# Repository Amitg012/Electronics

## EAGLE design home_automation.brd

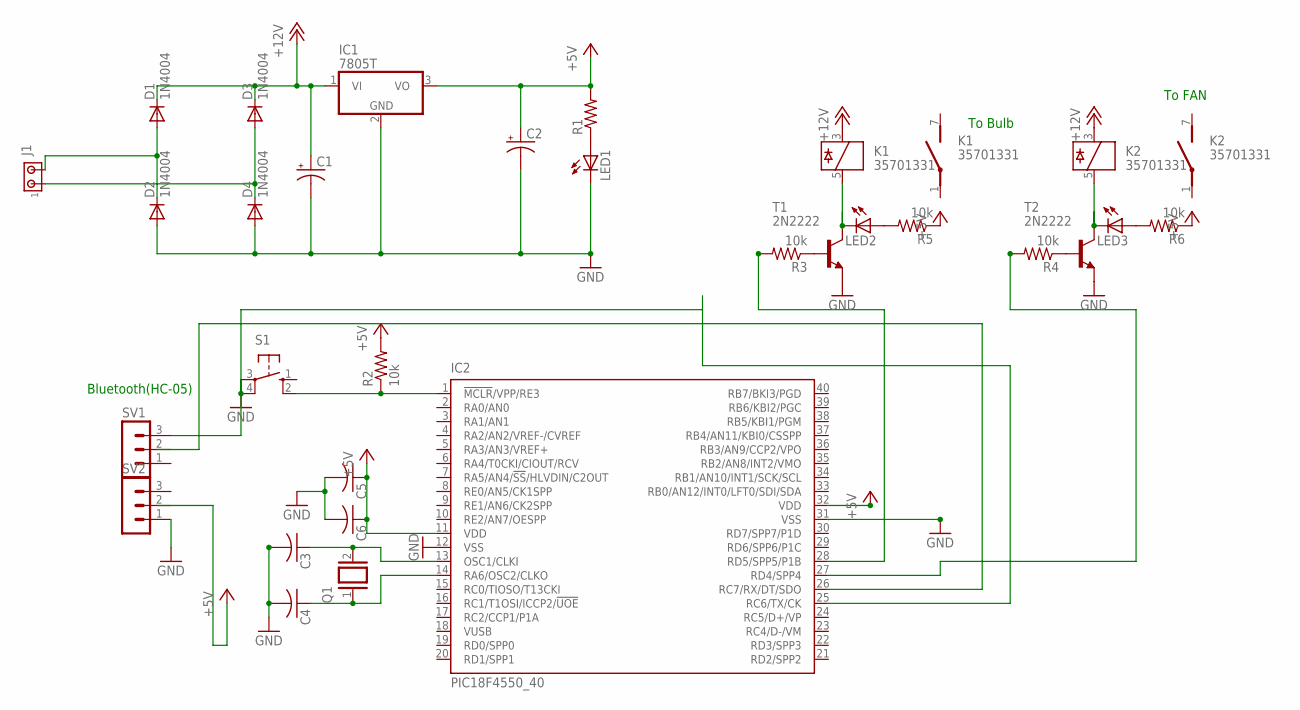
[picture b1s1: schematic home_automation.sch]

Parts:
C1, C2: CPOL-USE3.5-8; E3,5-8
C3, C4, C5, C6: C-US025-024X044; C025-024X044
D1, D2, D3, D4: 1N4004; DO41-10
IC1: 7805T; TO220H
IC2: PIC18F4550_40; DIL40
J1: MTA02-100; 10X02MTA
K1, K2: 35701331; REED
LED1, LED2, LED3: LED5MM
Q1: XTAL/S; QS
R1: R-US_0207/10; 0207/10
R2, R3, R4, R5, R6: 10k; 0207/10
S1: 10-XX; B3F-10XX
SV1, SV2: MA03-1
T1, T2: 2N2222; TO92-EBC-OVAL

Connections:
+5V: C2.+, C5.1, C6.1, IC1.3 (VO), IC2.11 (VDD), IC2.32 (VDD), R1.2, R2.2, R5.1, R6.1
+12V: C1.+, D1.C, D3.C, IC1.1 (VI), K1.3, K2.3
GND: C1.-, C2.-, C3.2, C4.2, C5.2, C6.2, D2.A, D4.A, IC1.2 (GND), IC2.12 (VSS), IC2.31 (VSS), LED1.K (C), S1.3, S1.4 (P1), SV2.1, T1.E, T2.E
unnamed: IC2.25 (RC6/TX/CK), SV1.3
unnamed: D1.A, D2.C, J1.2
unnamed: D3.A, D4.C, J1.1
unnamed: C4.1, IC2.14 (RA6/OSC2/CLKO), Q1.1
unnamed: C3.1, IC2.13 (OSC1/CLKI), Q1.2
unnamed: LED1.A, R1.1
unnamed: LED2.A, R5.2
unnamed: R4.1, T2.B
unnamed: K2.5, LED3.K (C), T2.C
unnamed: R3.1, T1.B
unnamed: IC2.1 (!MCLR!/VPP/RE3), R2.1, S1.2 (S1)
unnamed: LED3.A, R6.2
unnamed: IC2.27 (RD4/SPP4), R4.2
unnamed: K1.5, LED2.K (C), T1.C
unnamed: IC2.28 (RD5/SPP5/P1B), R3.2

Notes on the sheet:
To Bulb
To FAN
Bluetooth(HC-05)

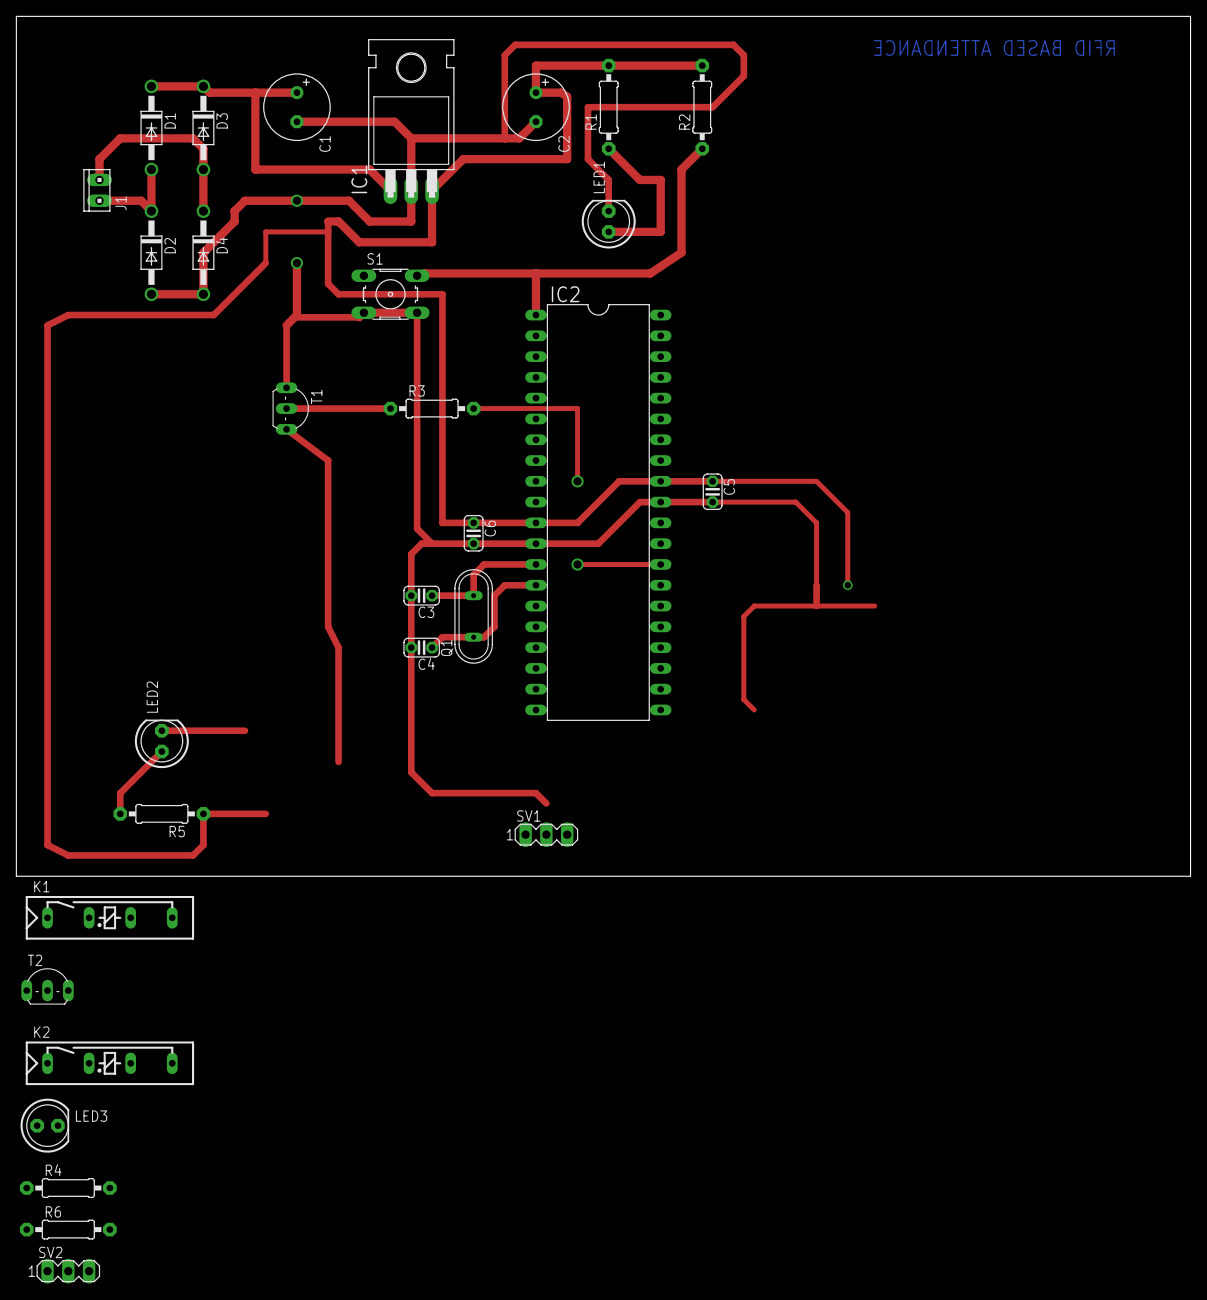
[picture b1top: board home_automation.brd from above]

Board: 2 copper layers, 143.5 x 105.1 mm, 30 parts (0 on the bottom side), 18 nets.

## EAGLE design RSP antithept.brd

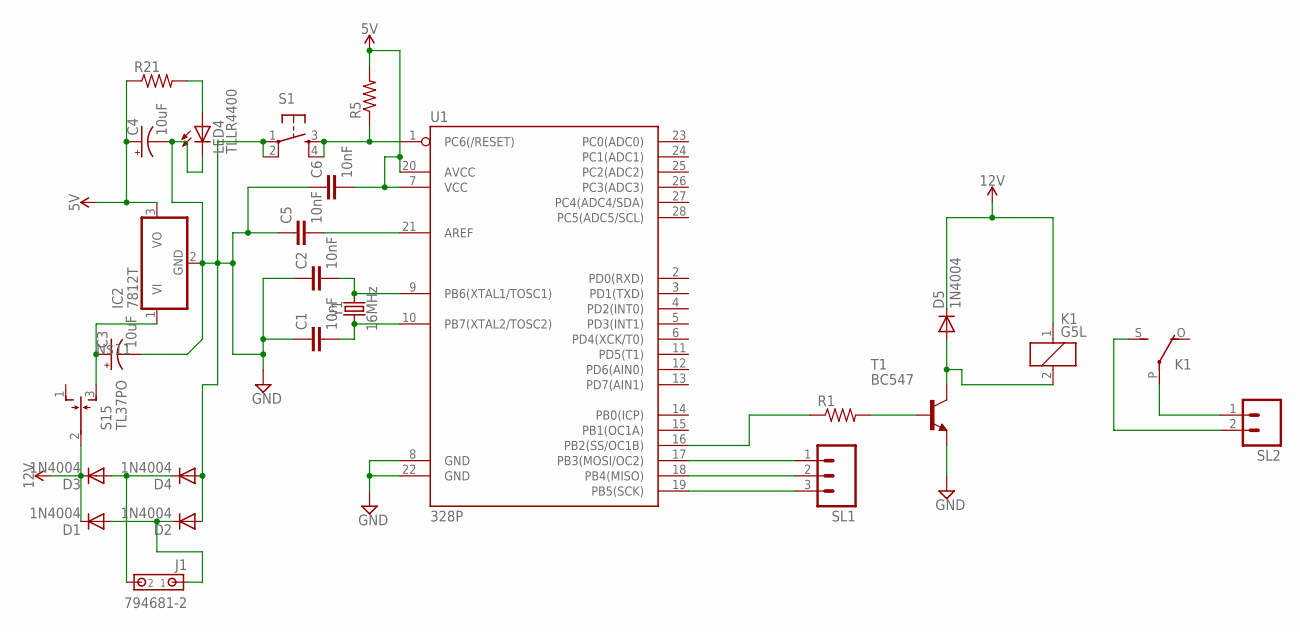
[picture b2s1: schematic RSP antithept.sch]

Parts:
C1, C2, C5, C6: 10nF; CAP-PTH-10MM
C3, C4: 10uF; CPOL-RADIAL-2.5MM-5MM-KIT
D1, D2, D3, D4, D5: 1N4004; DO41-10
IC2: 7812T; TO220H
J1: 794681-2
K1: G5L; G5LE
LED4: TLLR4400; LED3MM
R1: R-US_0207/9; 0207/9
R5, R21: R-US_0207/12; 0207/12
S1: TAC_SWITCHPTH; TACTILE-PTH
S15: TL37PO; TL3XPO
SL1: MA03; 03P
SL2: MA02; 02PA
T1: BC547; TO92
U1: 328P; DIP28
Y1: 16MHz; HC49US

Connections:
5V: C4.1 (+), C6.2, IC2.3 (VO), R5.2, R21.1, U1.7 (VCC), U1.20 (AVCC)
12V: D1.C, D3.C, D5.C, K1.1, S15.2
GND: C1.1, C2.1, C3.2 (-), C4.2 (-), C5.1, C6.1, D2.A, D4.A, IC2.2 (GND), LED4.K (C), S1.1, S1.2, T1.1 (E), U1.8 (GND), U1.22 (GND)
unnamed: SL1.1, U1.17 (PB3(MOSI/OC2))
unnamed: SL1.2, U1.18 (PB4(MISO))
unnamed: C2.2, U1.9 (PB6(XTAL1/TOSC1)), Y1.2
unnamed: C1.2, U1.10 (PB7(XTAL2/TOSC2)), Y1.1
unnamed: LED4.A, R21.2
unnamed: C5.2, U1.21 (AREF)
unnamed: SL1.3, U1.19 (PB5(SCK))
unnamed: R1.1, U1.16 (PB2(SS/OC1B))
unnamed: R5.1, S1.3, S1.4, U1.1 (PC6(/RESET))
unnamed: D3.A, D4.C, J1.2
unnamed: C3.1 (+), IC2.1 (VI), S15.3 (S)
unnamed: R1.2, T1.2 (B)
unnamed: D5.A, K1.2, T1.3 (C)
unnamed: K1.S, SL2.2
unnamed: K1.P, SL2.1
unnamed: D1.A, D2.C, J1.1

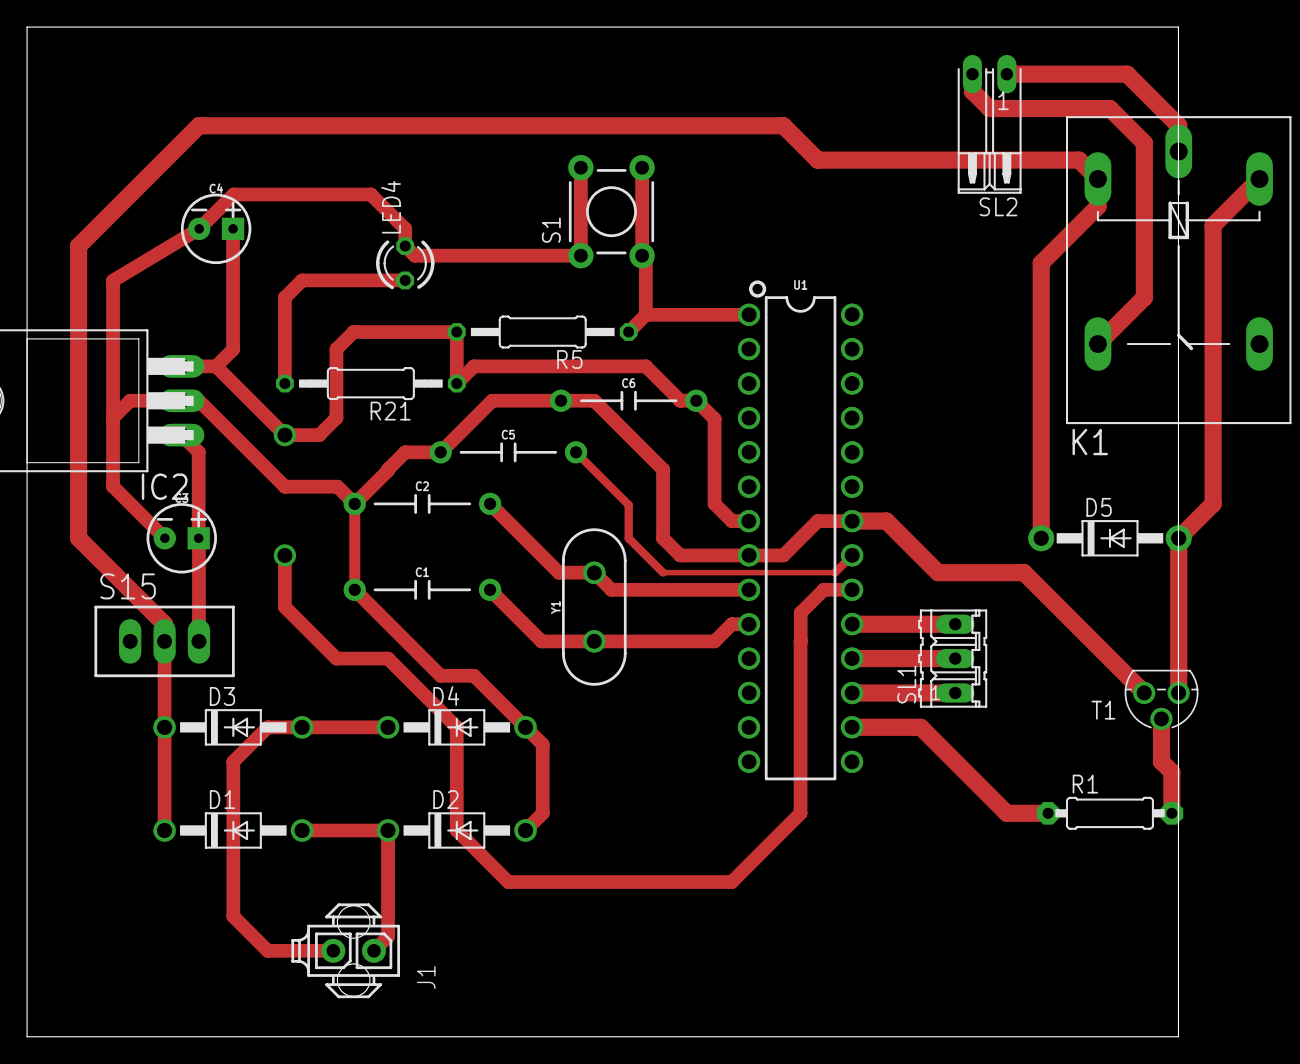
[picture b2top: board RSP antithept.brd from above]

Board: 2 copper layers, 85.1 x 74.6 mm, 25 parts (0 on the bottom side), 19 nets.

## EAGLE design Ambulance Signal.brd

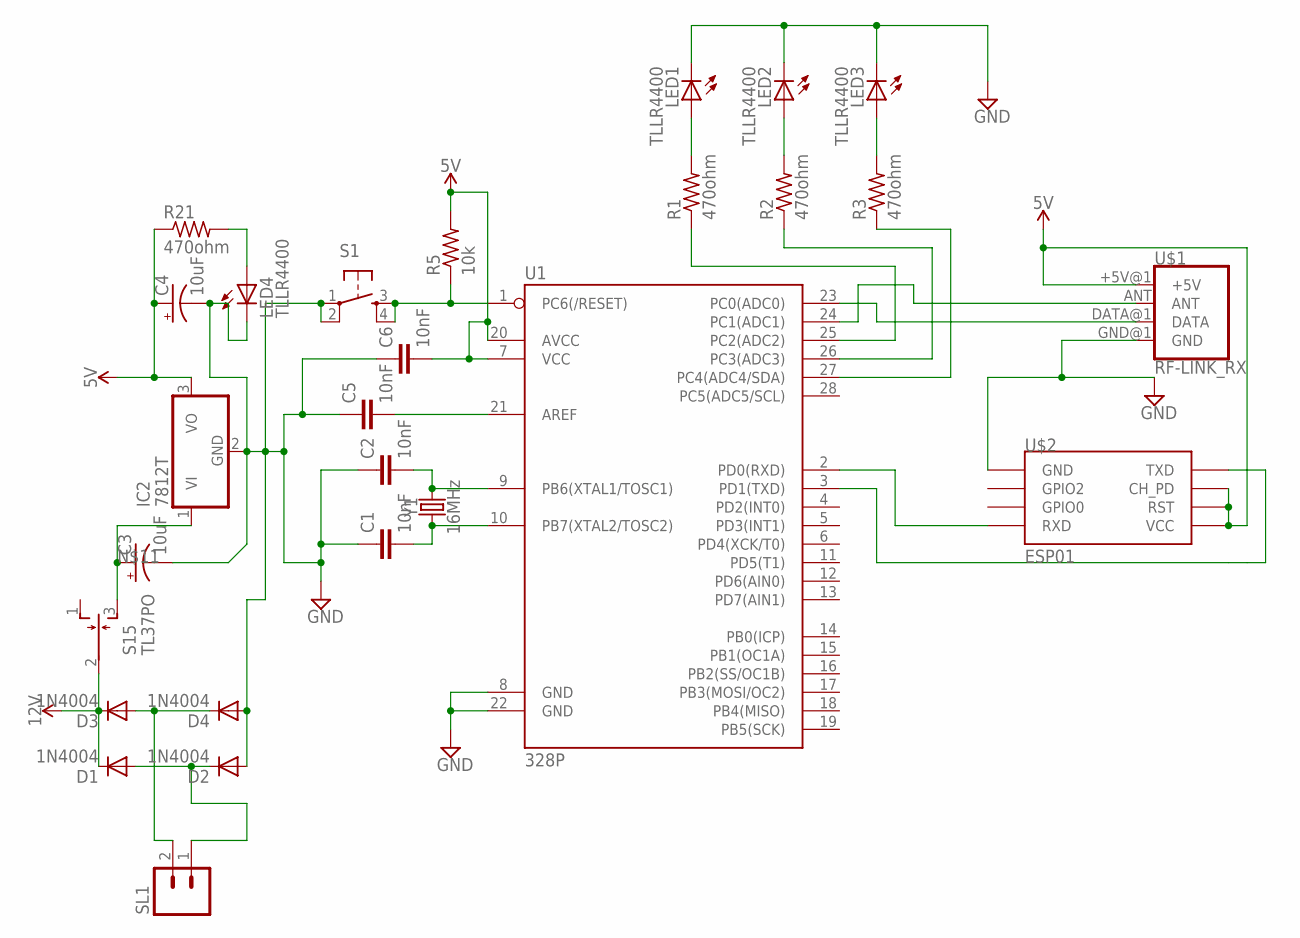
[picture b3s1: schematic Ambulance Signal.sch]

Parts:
C1, C2, C5, C6: 10nF; CAP-PTH-10MM
C3, C4: 10uF; CPOL-RADIAL-2.5MM-5MM-KIT
D1, D2, D3, D4: 1N4004; DO41-10
IC2: 7812T; TO220H
LED1, LED2, LED3, LED4: TLLR4400; LED3MM
R1, R2, R3, R21: 470ohm; 0207/12
R5: 10k; 0207/12
S1: TAC_SWITCHPTH; TACTILE-PTH
S15: TL37PO; TL3XPO
SL1: MA02; 02PA
U1: 328P; DIP28
U$1: RF-LINK_RX
U$2: ESP01
Y1: 16MHz; HC49US

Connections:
5V: C4.1 (+), C6.2, IC2.3 (VO), R5.2, R21.1, U1.7 (VCC), U1.20 (AVCC), U$1.+5V@1 (+5V), U$2.CH_PD, U$2.RST, U$2.VCC
12V: D1.C, D3.C, S15.2
GND: C1.1, C2.1, C3.2 (-), C4.2 (-), C5.1, C6.1, D2.A, D4.A, IC2.2 (GND), LED1.K (C), LED2.K (C), LED3.K (C), LED4.K (C), S1.1, S1.2, U1.8 (GND), U1.22 (GND), U$1.GND@1 (GND), U$2.GND
unnamed: U1.24 (PC1(ADC1)), U$1.ANT
unnamed: U1.23 (PC0(ADC0)), U$1.DATA@1 (DATA)
unnamed: C2.2, U1.9 (PB6(XTAL1/TOSC1)), Y1.2
unnamed: C1.2, U1.10 (PB7(XTAL2/TOSC2)), Y1.1
unnamed: LED4.A, R21.2
unnamed: C5.2, U1.21 (AREF)
unnamed: R5.1, S1.3, S1.4, U1.1 (PC6(/RESET))
unnamed: D3.A, D4.C, SL1.2
unnamed: C3.1 (+), IC2.1 (VI), S15.3 (S)
unnamed: U1.2 (PD0(RXD)), U$2.RX (RXD)
unnamed: U1.3 (PD1(TXD)), U$2.TX (TXD)
unnamed: R1.1, U1.25 (PC2(ADC2))
unnamed: R2.1, U1.26 (PC3(ADC3))
unnamed: R3.1, U1.27 (PC4(ADC4/SDA))
unnamed: LED1.A, R1.2
unnamed: LED2.A, R2.2
unnamed: LED3.A, R3.2
unnamed: D1.A, D2.C, SL1.1

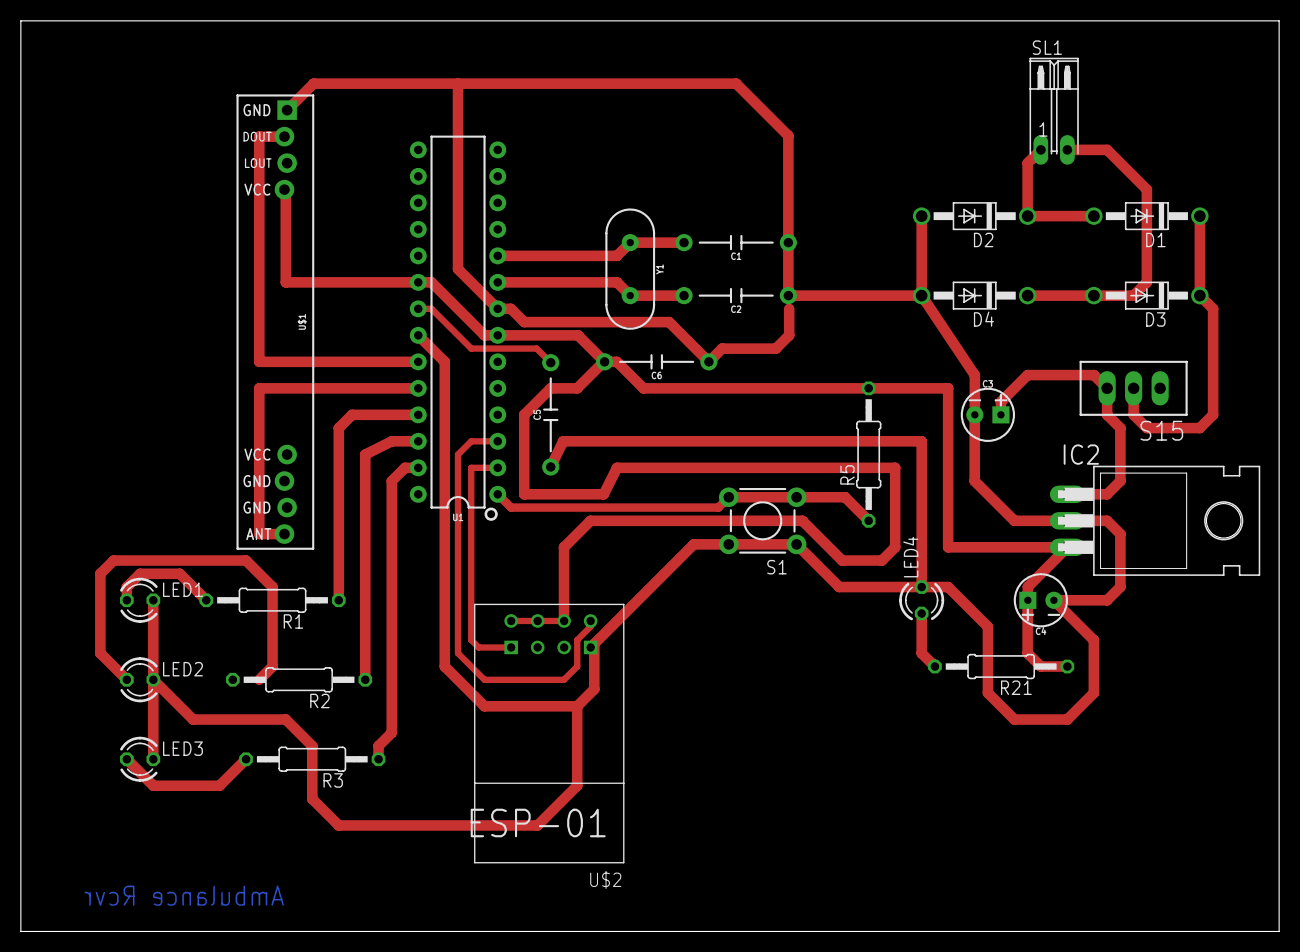
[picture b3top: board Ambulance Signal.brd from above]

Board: 2 copper layers, 120.6 x 87.3 mm, 27 parts (0 on the bottom side), 21 nets.

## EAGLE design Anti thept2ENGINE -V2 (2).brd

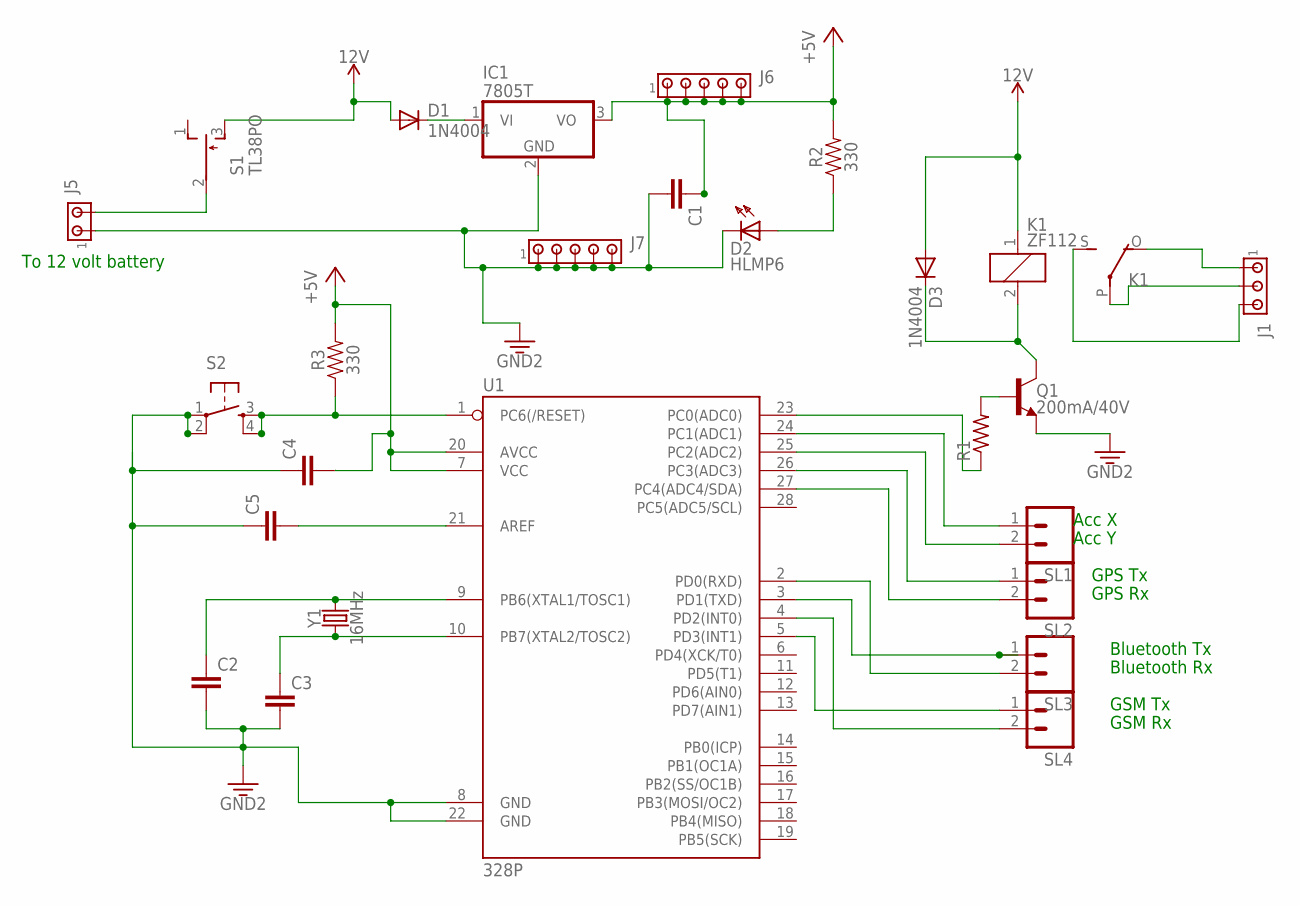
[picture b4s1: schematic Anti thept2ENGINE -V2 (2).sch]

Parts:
C1, C2, C3, C4, C5: C5/2.5; C5B2.5
D1, D3: 1N4004; DO41-10
D2: HLMP6
IC1: 7805T; TO220H
J1: MTA03-156; 1X3MTA
J5: MTA02-156; 1X2MTA
J6, J7: MTA05-100; 10X05MTA
K1: ZF112
Q1: 200mA/40V; TO-92
R1: R-US_0204/7; 0204/7
R2, R3: 330; AXIAL-0.3
S1: TL38PO; TL3XPO
S2: TAC_SWITCHPTH; TACTILE-PTH
SL1, SL2, SL3, SL4: MA02; 02PA
U1: 328P; DIP28
Y1: 16MHz; HC49US

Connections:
3.3V: C1.2, C2.2, C3.2, C4.1, C5.1, D2.K, IC1.2 (GND), J5.1, J7.1, J7.2, J7.3, J7.4, J7.5, Q1.1 (E), S2.1, S2.2, U1.8 (GND), U1.22 (GND)
12V: D1.A, D3.A, K1.1, S1.3 (S)
+5V: C1.1, C4.2, IC1.3 (VO), J6.1, J6.2, J6.3, J6.4, J6.5, R2.P$2 (2), R3.P$2 (2), U1.7 (VCC), U1.20 (AVCC)
unnamed: J1.1, K1.O
unnamed: J1.2, K1.P
unnamed: Q1.2 (B), R1.2
unnamed: D3.C, K1.2, Q1.3 (C)
unnamed: J1.3, K1.S
unnamed: R1.1, U1.23 (PC0(ADC0))
unnamed: D2.A, R2.P$1 (1)
unnamed: C3.1, U1.10 (PB7(XTAL2/TOSC2)), Y1.1
unnamed: SL1.1, U1.24 (PC1(ADC1))
unnamed: R3.P$1 (1), S2.3, S2.4, U1.1 (PC6(/RESET))
unnamed: SL1.2, U1.25 (PC2(ADC2))
unnamed: C5.2, U1.21 (AREF)
unnamed: SL2.1, U1.26 (PC3(ADC3))
unnamed: J5.2, S1.2
unnamed: SL3.2, U1.2 (PD0(RXD))
unnamed: D1.C, IC1.1 (VI)
unnamed: SL3.1, U1.3 (PD1(TXD))
unnamed: C2.1, U1.9 (PB6(XTAL1/TOSC1)), Y1.2
unnamed: SL2.2, U1.27 (PC4(ADC4/SDA))
unnamed: SL4.2, U1.4 (PD2(INT0))
unnamed: SL4.1, U1.5 (PD3(INT1))

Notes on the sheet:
Bluetooth Tx
Bluetooth Rx
GPS Tx
GPS Rx
Acc X
Acc Y
GSM Tx
GSM Rx
To 12 volt battery

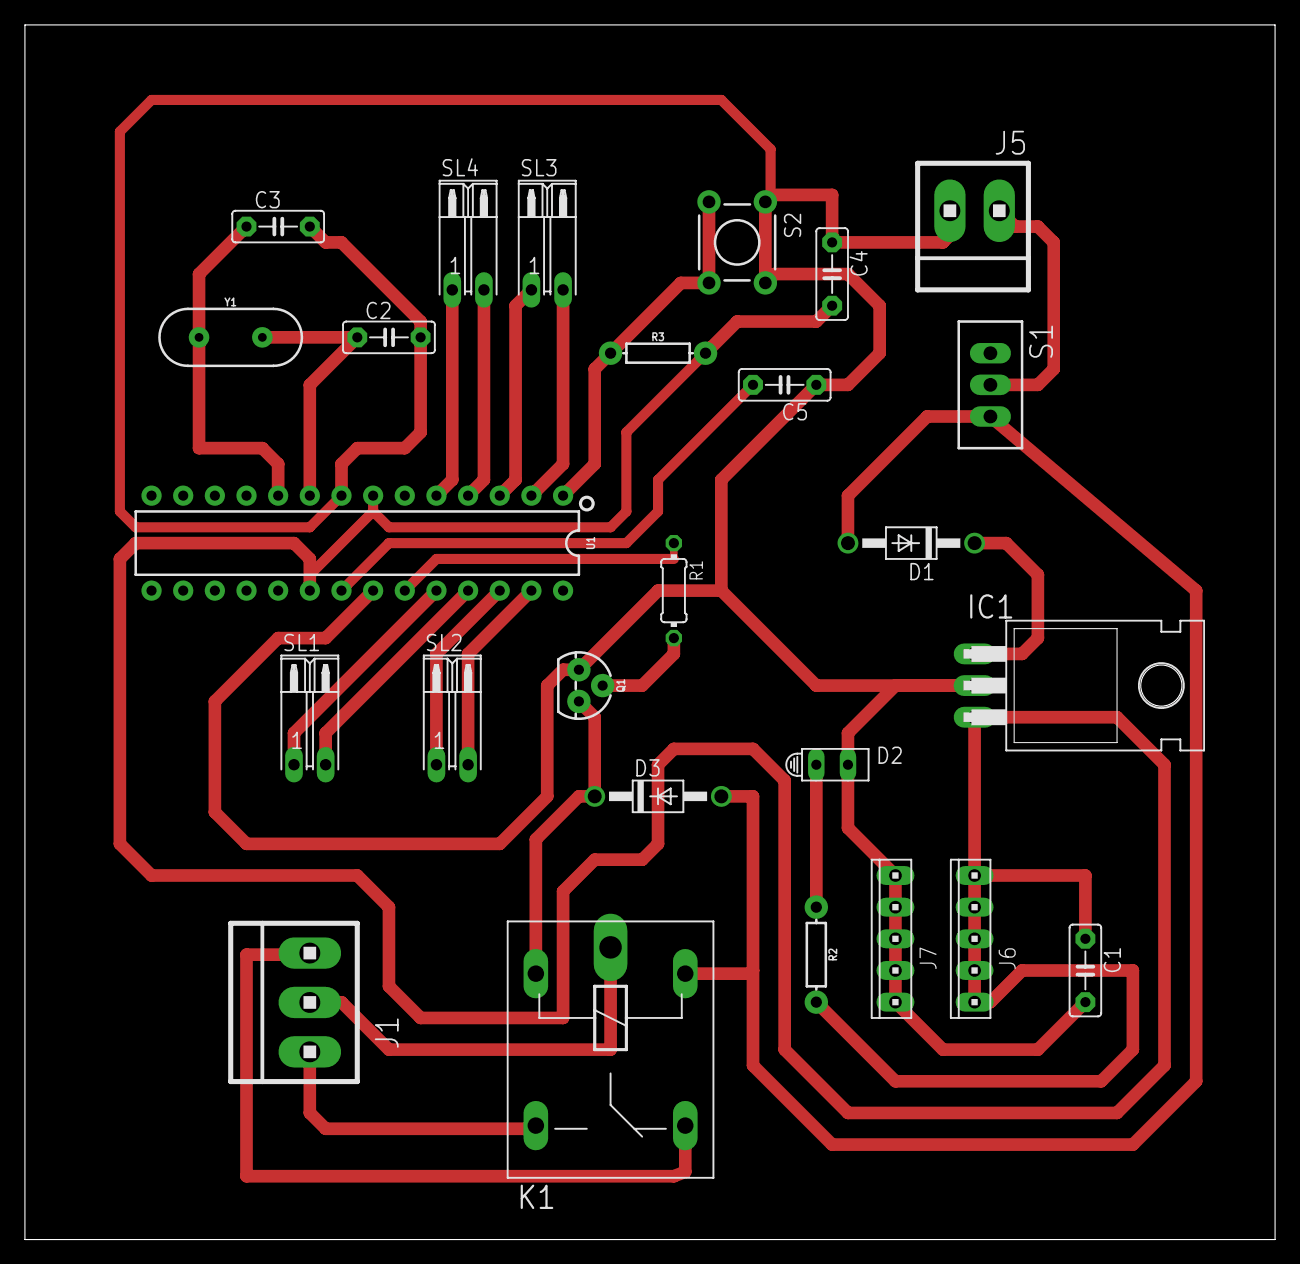
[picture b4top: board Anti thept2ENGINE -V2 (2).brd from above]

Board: 2 copper layers, 100.3 x 97.5 mm, 26 parts (0 on the bottom side), 24 nets.

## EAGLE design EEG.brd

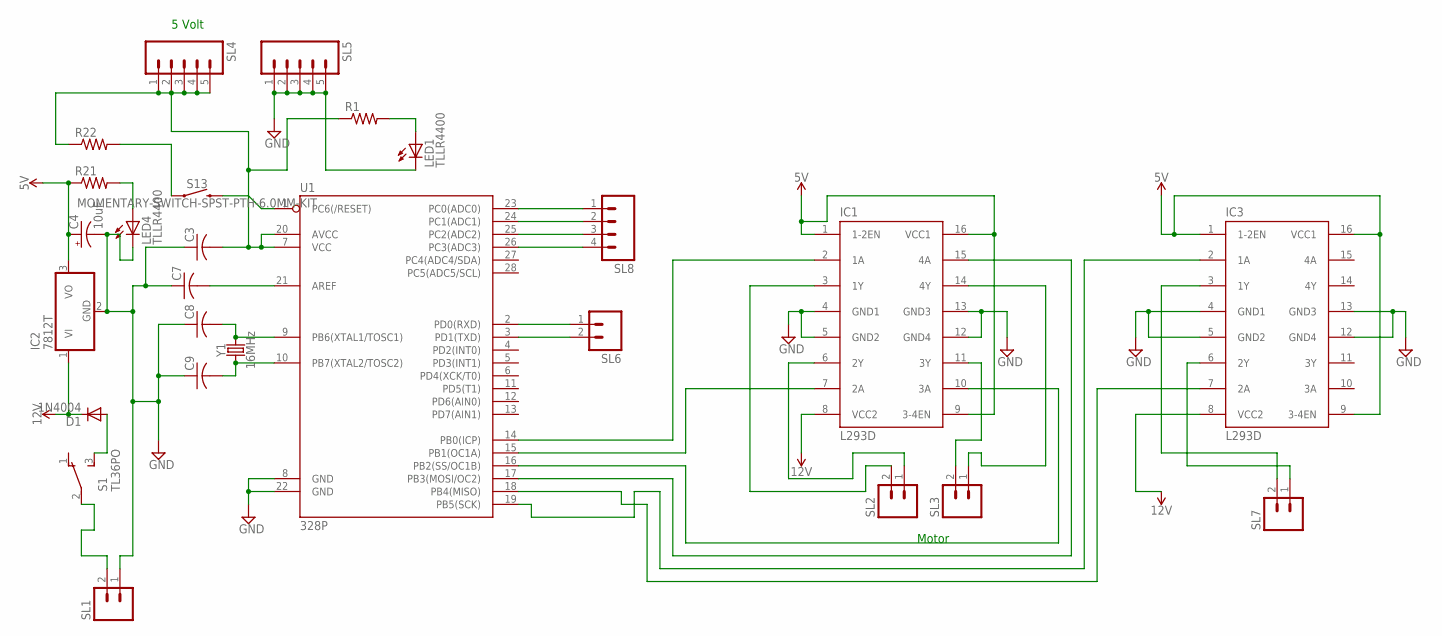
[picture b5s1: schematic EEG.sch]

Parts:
C3, C7, C8, C9: C-US025-025X050; C025-025X050
C4: 10uF; CPOL-RADIAL-2.5MM-5MM-KIT
D1: 1N4004; DO41-10
IC1, IC3: L293D; DIL16
IC2: 7812T; TO220H
LED1, LED4: TLLR4400; LED3MM
R1, R21, R22: R-US_0207/12; 0207/12
S1: TL36PO; TL3XPO
S13: MOMENTARY-SWITCH-SPST-PTH-6.0MM-KIT; TACTILE_SWITCH_PTH_6.0MM_KIT
SL1, SL2, SL3, SL6, SL7: MA02; 02PA
SL4, SL5: MA05; 05PA
SL8: MA04; 04PA
U1: 328P; DIP28
Y1: 16MHz; HC49US

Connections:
5V: C4.1 (+), IC1.1 (1-2EN), IC1.9 (3-4EN), IC1.16 (VCC1), IC2.3 (VO), IC3.1 (1-2EN), IC3.9 (3-4EN), IC3.16 (VCC1), R21.1
12V: D1.C, IC1.8 (VCC2), IC2.1 (VI), IC3.8 (VCC2)
GND: C3.1, C4.2 (-), C7.1, C8.1, C9.1, IC1.4 (GND1), IC1.5 (GND2), IC1.12 (GND4), IC1.13 (GND3), IC2.2 (GND), IC3.4 (GND1), IC3.5 (GND2), IC3.12 (GND4), IC3.13 (GND3), LED1.K (C), LED4.K (C), SL1.1, SL5.1, SL5.2, SL5.3, SL5.4, SL5.5, U1.8 (GND), U1.22 (GND)
unnamed: C7.2, U1.21 (AREF)
unnamed: S1.2, SL1.2
unnamed: C8.2, U1.9 (PB6(XTAL1/TOSC1)), Y1.2
unnamed: C9.2, U1.10 (PB7(XTAL2/TOSC2)), Y1.1
unnamed: LED4.A, R21.2
unnamed: D1.A, S1.3 (S)
unnamed: IC1.3 (1Y), SL2.2
unnamed: R22.2, S13.1
unnamed: S13.3 (2), U1.1 (PC6(/RESET))
unnamed: IC3.2 (1A), U1.19 (PB5(SCK))
unnamed: IC3.7 (2A), U1.18 (PB4(MISO))
unnamed: IC3.3 (1Y), SL7.2
unnamed: IC1.2 (1A), U1.14 (PB0(ICP))
unnamed: IC1.7 (2A), U1.15 (PB1(OC1A))
unnamed: IC1.10 (3A), U1.16 (PB2(SS/OC1B))
unnamed: IC1.15 (4A), U1.17 (PB3(MOSI/OC2))
unnamed: C3.2, R1.1, R22.1, SL4.1, SL4.2, SL4.3, SL4.4, SL4.5, U1.7 (VCC), U1.20 (AVCC)
unnamed: IC3.6 (2Y), SL7.1
unnamed: LED1.A, R1.2
unnamed: SL6.1, U1.2 (PD0(RXD))
unnamed: SL6.2, U1.3 (PD1(TXD))
unnamed: SL8.1, U1.23 (PC0(ADC0))
unnamed: SL8.2, U1.24 (PC1(ADC1))
unnamed: SL8.3, U1.25 (PC2(ADC2))
unnamed: SL8.4, U1.26 (PC3(ADC3))
unnamed: IC1.14 (4Y), SL3.1
unnamed: IC1.6 (2Y), SL2.1
unnamed: IC1.11 (3Y), SL3.2

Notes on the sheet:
Motor
5 Volt

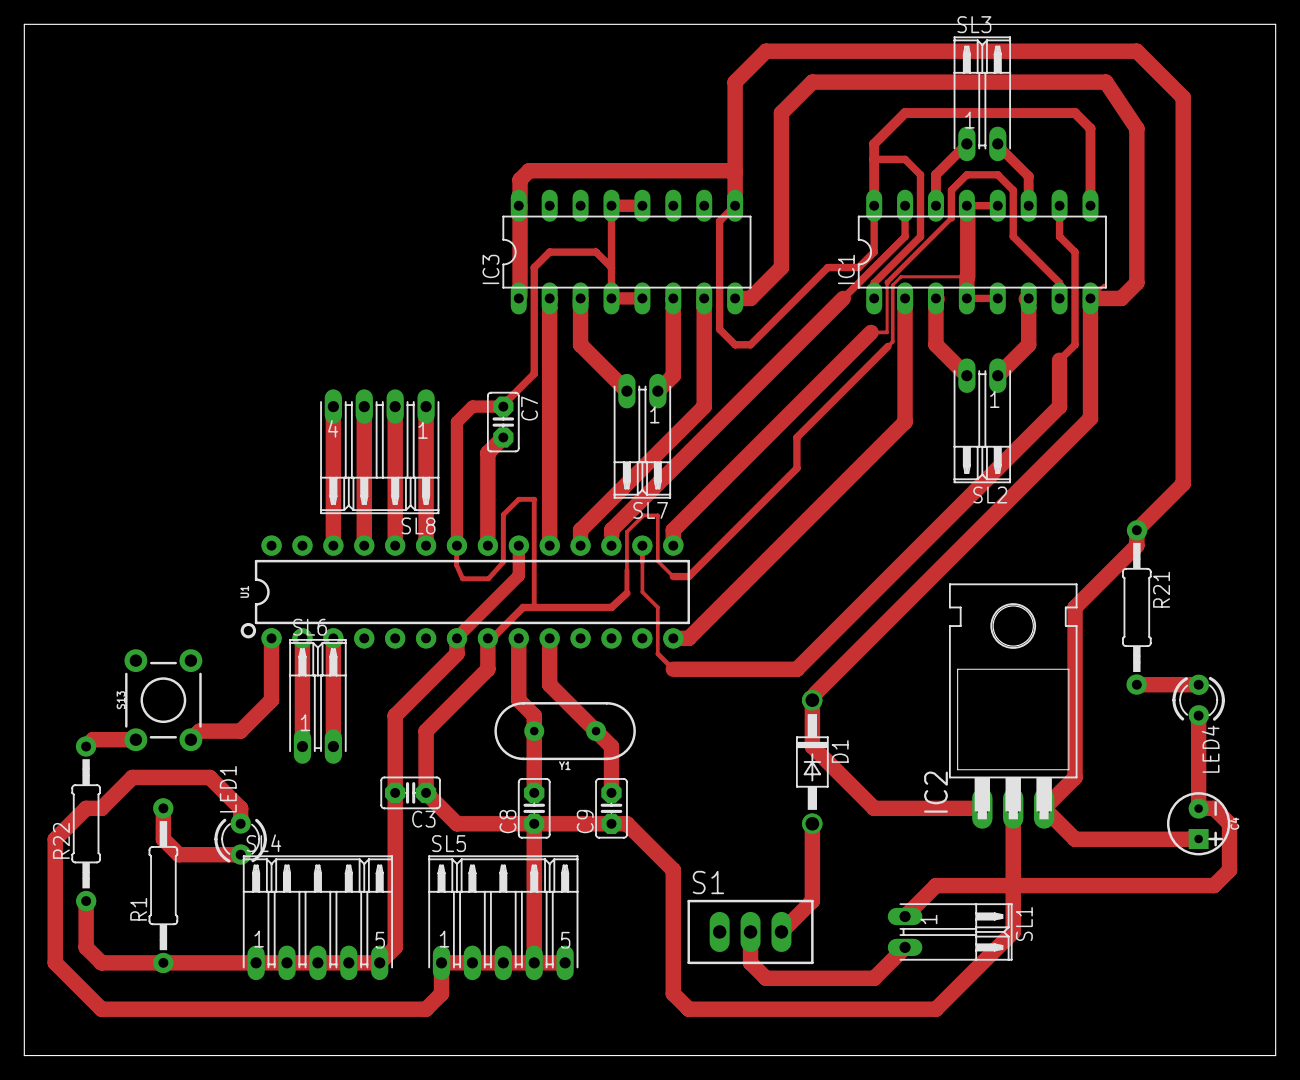
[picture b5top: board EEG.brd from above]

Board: 2 copper layers, 102.8 x 84.8 mm, 26 parts (0 on the bottom side), 31 nets.

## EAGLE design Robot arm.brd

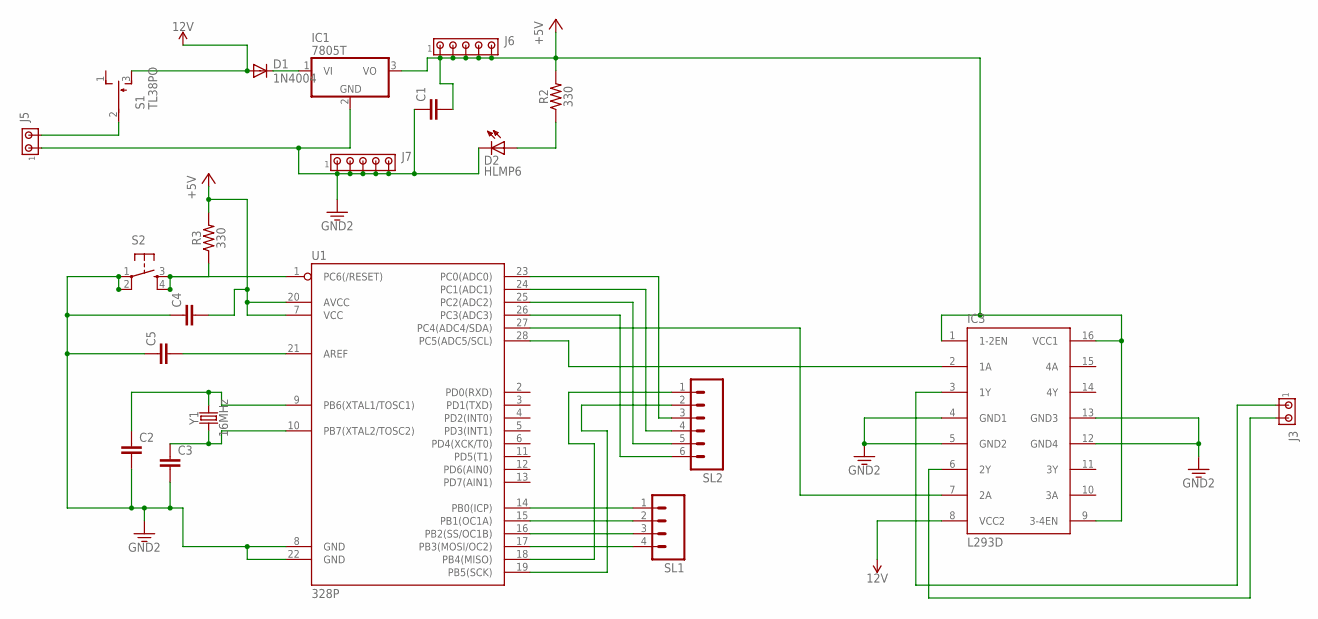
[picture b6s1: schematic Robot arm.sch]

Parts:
C1, C2, C3, C4, C5: C5/2.5; C5B2.5
D1: 1N4004; DO41-10
D2: HLMP6
IC1: 7805T; TO220H
IC3: L293D; DIL16
J3, J5: MTA02-156; 1X2MTA
J6, J7: MTA05-100; 10X05MTA
R2, R3: 330; AXIAL-0.3
S1: TL38PO; TL3XPO
S2: TAC_SWITCHPTH; TACTILE-PTH
SL1: MA04; 04PA
SL2: MA06; 06PA
U1: 328P; DIP28
Y1: 16MHz; HC49US

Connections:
3.3V: C1.1, C2.2, C3.2, C4.1, C5.1, D2.K, IC1.2 (GND), IC3.4 (GND1), IC3.5 (GND2), IC3.12 (GND4), IC3.13 (GND3), J5.1, J7.1, J7.2, J7.3, J7.4, J7.5, S2.1, S2.2, U1.8 (GND), U1.22 (GND)
12V: D1.A, IC3.8 (VCC2), S1.3 (S)
+5V: C1.2, C4.2, IC1.3 (VO), IC3.1 (1-2EN), IC3.9 (3-4EN), IC3.16 (VCC1), J6.1, J6.2, J6.3, J6.4, J6.5, R2.P$2 (2), R3.P$2 (2), U1.7 (VCC), U1.20 (AVCC)
unnamed: IC3.7 (2A), U1.27 (PC4(ADC4/SDA))
unnamed: SL1.1, U1.14 (PB0(ICP))
unnamed: SL1.2, U1.15 (PB1(OC1A))
unnamed: SL1.3, U1.16 (PB2(SS/OC1B))
unnamed: SL1.4, U1.17 (PB3(MOSI/OC2))
unnamed: SL2.3, U1.23 (PC0(ADC0))
unnamed: D2.A, R2.P$1 (1)
unnamed: IC3.2 (1A), U1.28 (PC5(ADC5/SCL))
unnamed: SL2.4, U1.24 (PC1(ADC1))
unnamed: R3.P$1 (1), S2.3, S2.4, U1.1 (PC6(/RESET))
unnamed: C3.1, U1.10 (PB7(XTAL2/TOSC2)), Y1.1
unnamed: C5.2, U1.21 (AREF)
unnamed: IC3.3 (1Y), J3.1
unnamed: J5.2, S1.2
unnamed: IC3.6 (2Y), J3.2
unnamed: D1.C, IC1.1 (VI)
unnamed: SL2.5, U1.25 (PC2(ADC2))
unnamed: SL2.6, U1.26 (PC3(ADC3))
unnamed: SL2.1, U1.18 (PB4(MISO))
unnamed: SL2.2, U1.19 (PB5(SCK))
unnamed: C2.1, U1.9 (PB6(XTAL1/TOSC1)), Y1.2

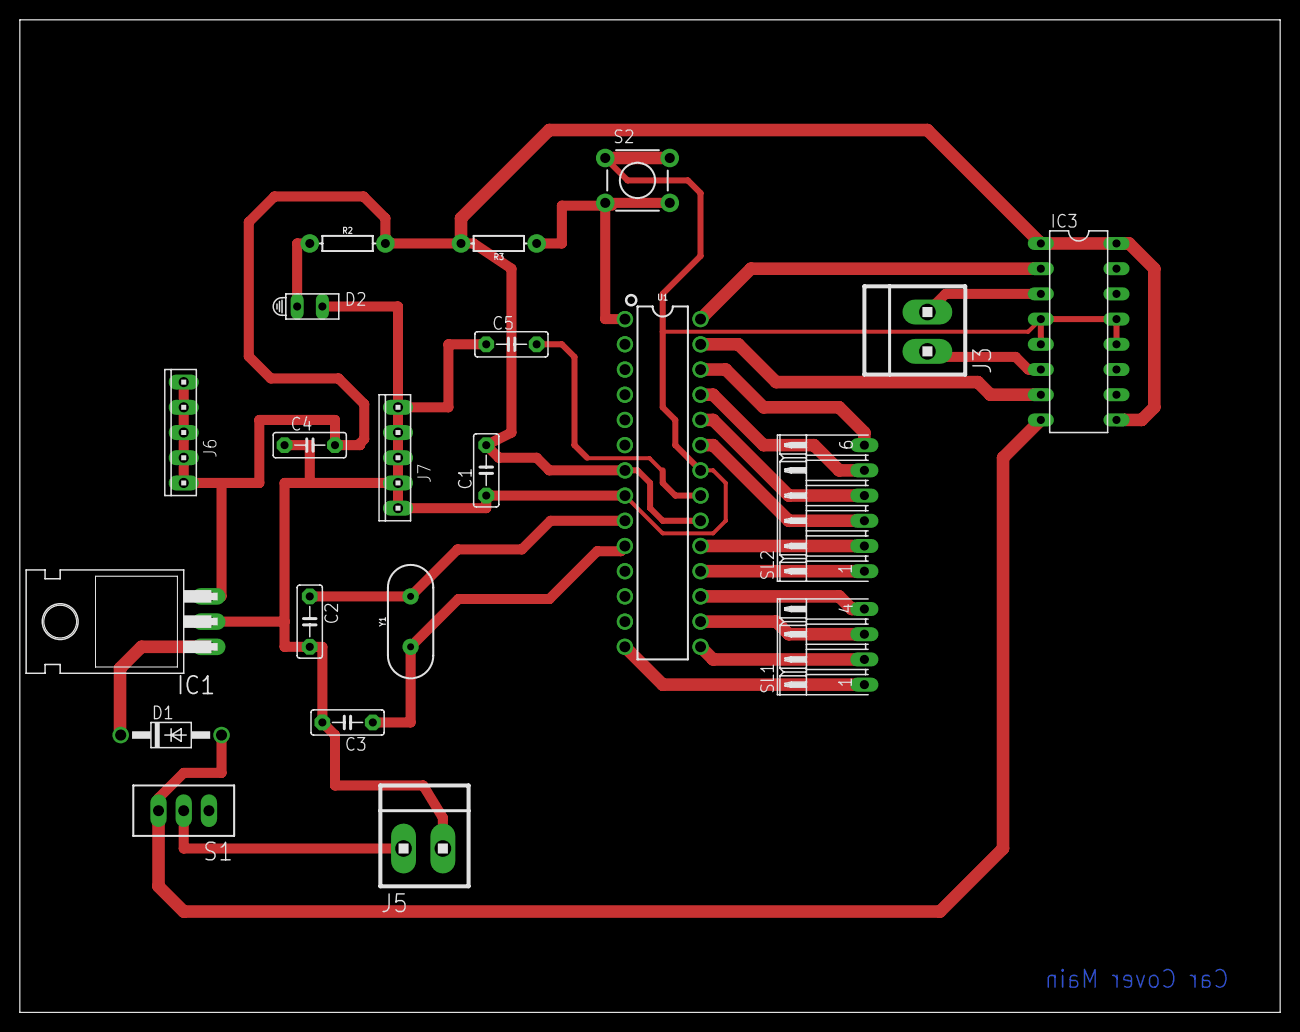
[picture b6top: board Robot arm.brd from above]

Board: 2 copper layers, 127.0 x 100.0 mm, 21 parts (0 on the bottom side), 24 nets.

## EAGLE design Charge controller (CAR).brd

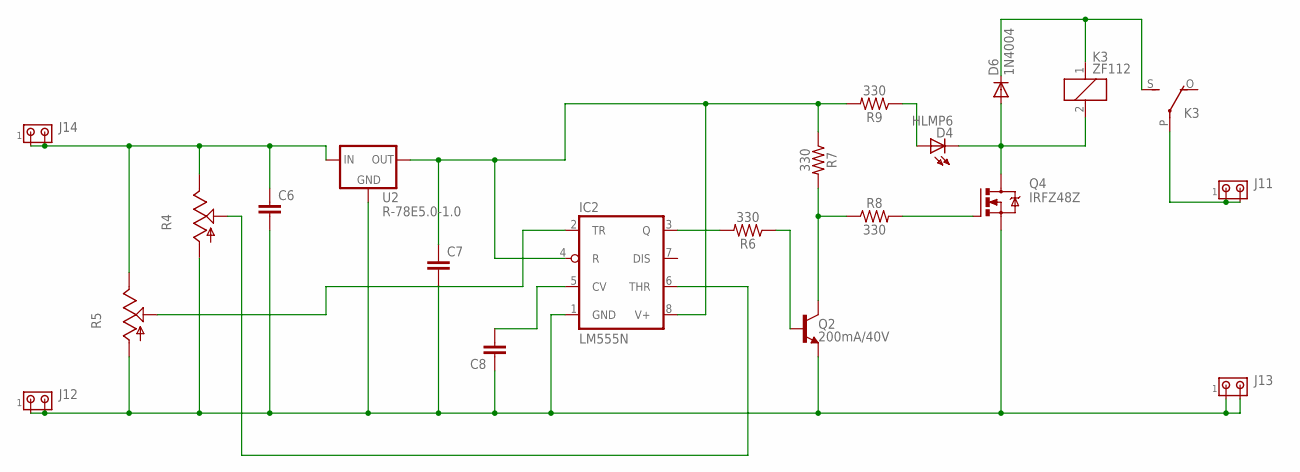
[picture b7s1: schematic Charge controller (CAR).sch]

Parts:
C6, C7, C8: C5/2.5; C5B2.5
D4: HLMP6
D6: 1N4004; DO41-10
IC2: LM555N; DIL08
J11, J12, J13, J14: MTA02-156; 1X2MTA
K3: ZF112
Q2: 200mA/40V; TO-92
Q4: IRFZ48Z; TO220BH
R4, R5: TRIM_US-CA6V; CA6V
R6, R7, R8, R9: 330; AXIAL-0.3
U2: R-78E5.0-1.0; DC-DC_CONVERTER_78XX

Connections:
unnamed: C6.1, J14.1, J14.2, R4.E, R5.E, U2.VIN (IN)
unnamed: C6.2, C7.2, C8.1, IC2.1 (GND), J12.1, J12.2, J13.1, J13.2, Q2.1 (E), Q4.S, R4.A, R5.A, U2.GND
unnamed: C7.1, IC2.4 (R), IC2.8 (V+), R7.P$1 (1), R9.P$2 (2), U2.VOUT (OUT)
unnamed: C8.2, IC2.5 (CV)
unnamed: IC2.2 (TR), R5.S
unnamed: D4.A, R9.P$1 (1)
unnamed: IC2.3 (Q), R6.P$2 (2)
unnamed: Q2.2 (B), R6.P$1 (1)
unnamed: Q2.3 (C), R7.P$2 (2), R8.P$1 (1)
unnamed: Q4.G, R8.P$2 (2)
unnamed: D4.K, D6.A, K3.2, Q4.D
unnamed: D6.C, K3.1, K3.S
unnamed: IC2.6 (THR), R4.S
unnamed: J11.1, J11.2, K3.P

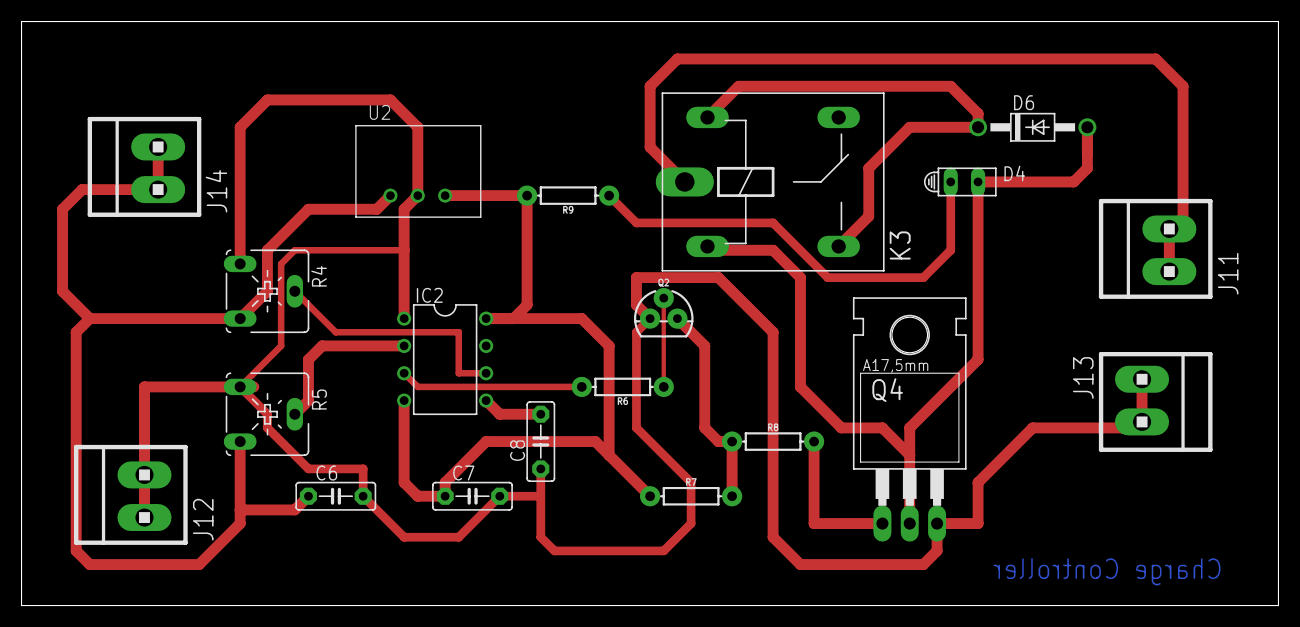
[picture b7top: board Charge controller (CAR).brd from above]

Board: 2 copper layers, 116.8 x 54.3 mm, 20 parts (0 on the bottom side), 14 nets.

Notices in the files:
parts and their libraries:
SparkFun-Capacitors: Licensing: Creative Commons ShareAlike 4.0 International - https://creativecommons.org/licenses/by-sa/4.0
